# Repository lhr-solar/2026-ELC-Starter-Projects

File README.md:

# 2026-ELC-Starter-Projects

## Goals
- Familiarize yourself with the basics of KiCad
- Learn how to make a schematic and place components into a layout
- Get used to submitting reviews, working on projects outside of workday, and using GitHub

## Repo Instructions
1. Clone the repo to your local machine
   
   ```git clone git@github.com:lhr-solar/2026-ELC-Starter-Projects.git```
2. In the repo, create a new branch with your name and check that the branch exists on the remote repo as well

   ```git checkout -b bevo```
3. Create a new KiCad project inside the folder with your name. When you create the project, make sure you DO NOT check the box that creates a new folder for the project.
4. Push your changes to the remote repository. Here are the commands you'll need to use + a more detailed [github guide](https://app.notion.com/p/lhrs/How-to-Git-3506309905da81729984d78645f975d0?source=copy_link)
   
   ``` git status``` -> Shows you the status report for all the files in your directory. Confirm that you're on the correct branch and NOT MAIN
   
   ``` git add .``` -> Adds all new, modified, and deleted files to the staging area (local action)
   
   ``` git commit -m "wow I made a repo"``` -> Saves a snapshot of the files from the staging area with a message (local action)
   
   ``` git push``` -> Saves the snapshot to the remote repo so everyone else can see your changes (remote action)
   
6. Follow the tutorials and keep learning! Push your changes frequently so you don't accidentally lose your progress if KiCad crashes (trust us on this one... it's not fun)

## Schematic
https://www.youtube.com/watch?v=nkHFoxe0mrU

Don't worry if his KiCad looks different from yours, this was made in 7 and we're using 10.

## Layout
https://www.youtube.com/watch?v=PlXd3lLZ4vc

Try to attempt the layout yourself before trying Phil's version. Make sure you push your trial run to Github before redoing it with Phil

## Advice
- Ask tons of questions! Make them public so everyone can learn!
- Come to review council to talk through your designs and reasoning
- Question everything! Learn why we do things a certain way so that you become a better engineer

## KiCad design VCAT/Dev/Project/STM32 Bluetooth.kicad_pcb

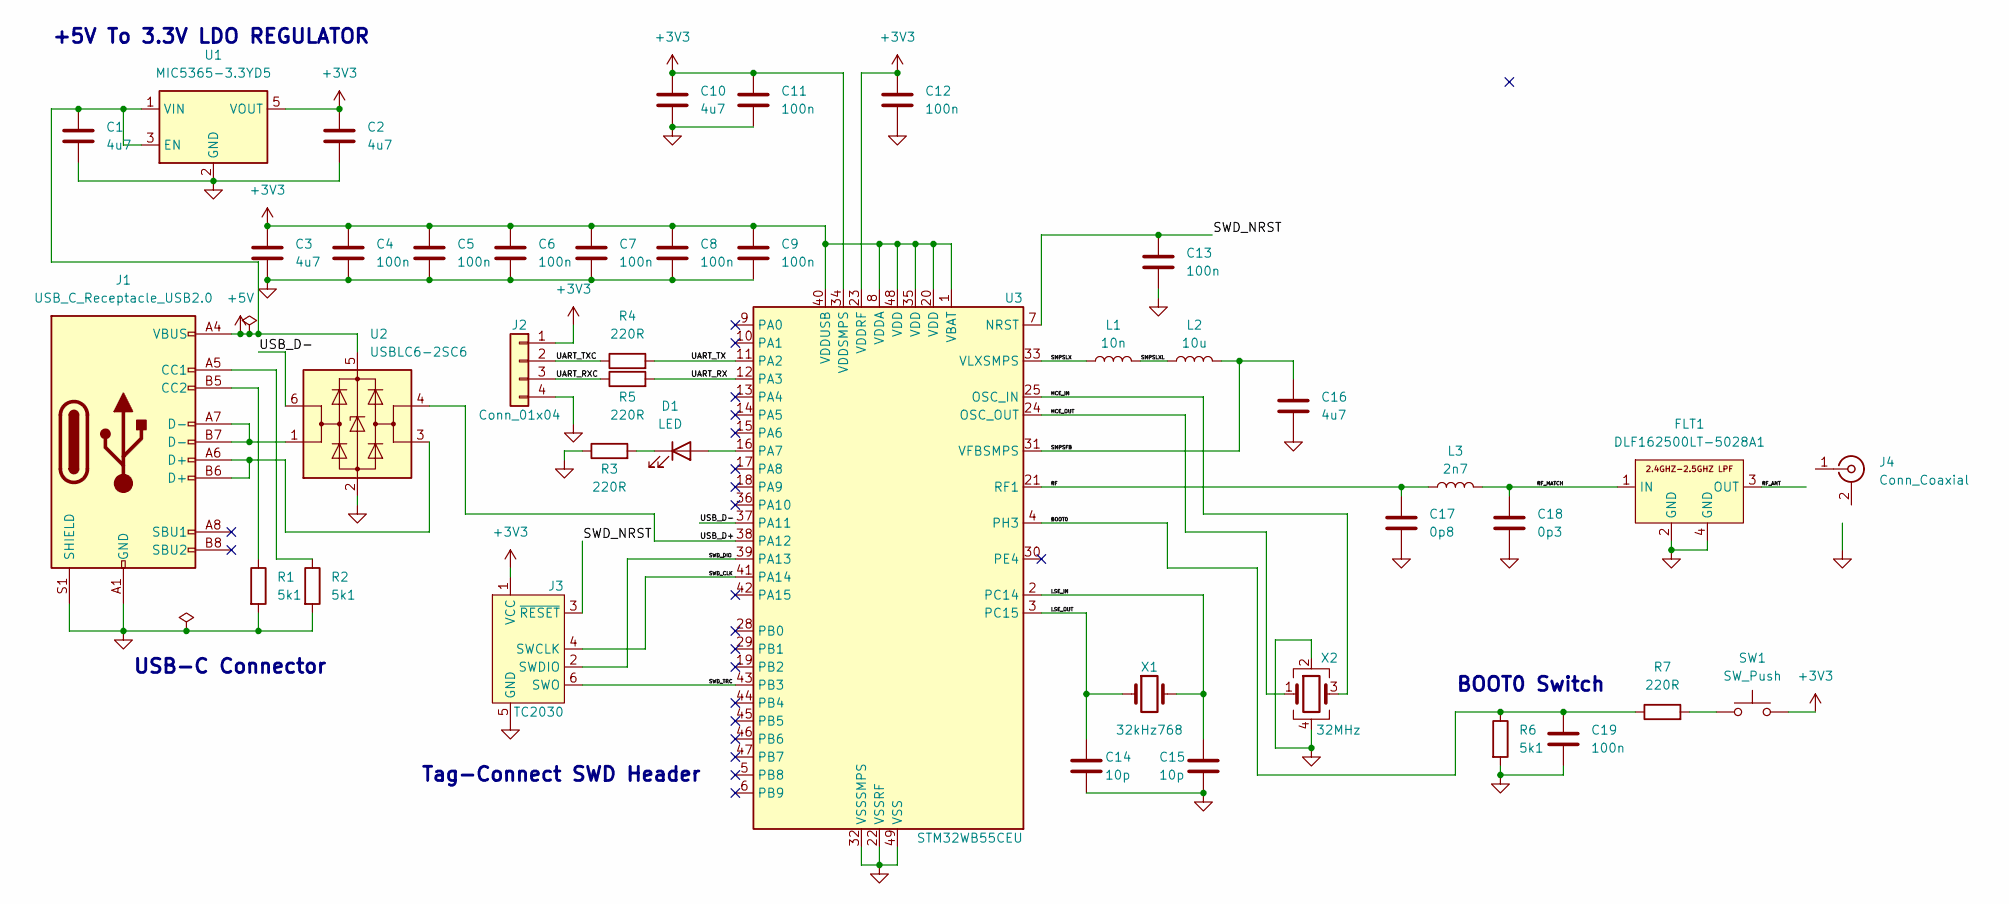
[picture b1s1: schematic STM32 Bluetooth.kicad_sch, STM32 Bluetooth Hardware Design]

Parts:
C1, C2, C3, C10, C16: 4u7; C_0603_1608Metric
C4, C5, C6, C7, C8, C9, C11, C12, C13, C19: 100n; C_0402_1005Metric
C14, C15: 10p; C_0402_1005Metric
C17: 0p8; C_0402_1005Metric
C18: 0p3; C_0402_1005Metric
D1: LED; LED_0402_1005Metric
FLT1: DLF162500LT-5028A1
J1: USB_C_Receptacle_USB2.0; USB_C_Receptacle_GCT_USB4105-xx-A_16P_TopMnt_Horizontal
J2: Conn_01x04; Molex_PicoBlade_53048-0410_1x04_P1.25mm_Horizontal
J3: TC2030; Tag-Connect_TC2030-IDC-FP_2x03_P1.27mm_Vertical
J4: Conn_Coaxial; U.FL_Hirose_U.FL-R-SMT-1_Vertical
L1: 10n; L_0402_1005Metric
L2: 10u; L_0805_2012Metric
L3: 2n7; L_0402_1005Metric
R1, R2, R6: 5k1; R_0402_1005Metric
R3, R4, R5, R7: 220R; R_0402_1005Metric
SW1: SW_Push; SW_SPST_CK_RS282G05A3
U1: MIC5365-3.3YD5; SOT-23-5
U2: USBLC6-2SC6; SOT-23-6
U3: STM32WB55CEU; QFN-48-1EP_7x7mm_P0.5mm_EP5.6x5.6mm
X1: 32kHz768; Crystal_SMD_2012-2Pin_2.0x1.2mm
X2: 32MHz; Crystal_SMD_2016-4Pin_2.0x1.6mm

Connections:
+3V3: C2.1, C3.1, C4.1, C5.1, C6.1, C7.1, C8.1, C9.1, C10.1, C11.1, C12.1, J2.1, J3.1 (VCC), SW1.2, U1.5 (VOUT), U3.1 (VBAT), U3.8 (VDDA), U3.20 (VDD), U3.23 (VDDRF), U3.34 (VDDSMPS), U3.35 (VDD), U3.40 (VDDUSB), U3.48 (VDD)
+5V: C1.1, J1.A4 (VBUS), J1.A9 (VBUS), J1.B4 (VBUS), J1.B9 (VBUS), U1.1 (VIN), U1.3 (EN), U2.5 (VBUS)
/BOOT0: C19.1, R6.1, R7.1, U3.4 (PH3)
/HCE_IN: U3.25 (OSC_IN), X2.3
/HCE_OUT: U3.24 (OSC_OUT), X2.1
/LSE_IN: C15.1, U3.2 (PC14), X1.2
/LSE_OUT: C14.1, U3.3 (PC15), X1.1
/RF: C17.1, L3.1, U3.21 (RF1)
/RF_ANT: FLT1.3 (OUT), J4.1 (In)
/RF_MATCH: C18.1, FLT1.1 (IN), L3.2
/SMPSFB: C16.1, L2.2, U3.31 (VFBSMPS)
/SMPSLX: L1.1, U3.33 (VLXSMPS)
/SMPSLXL: L1.2, L2.1
/SWD_CLK: J3.4 (SWCLK), U3.41 (PA14)
/SWD_DIO: J3.2 (SWDIO), U3.39 (PA13)
/SWD_NRST: C13.1, J3.3 (~RESET), U3.7 (NRST)
/SWD_TRC: J3.6 (SWO), U3.43 (PB3)
/UART_RX: R5.2, U3.12 (PA3)
/UART_RXC: J2.3, R5.1
/UART_TX: R4.2, U3.11 (PA2)
/UART_TXC: J2.2, R4.1
/USB_D+: U2.4 (I/O2), U3.38 (PA12)
/USB_D-: U2.6 (I/O1), U3.37 (PA11)
GND: C1.2, C2.2, C3.2, C4.2, C5.2, C6.2, C7.2, C8.2, C9.2, C10.2, C11.2, C12.2, C13.2, C14.2, C15.2, C16.2, C17.2, C18.2, C19.2, FLT1.2 (GND), FLT1.4 (GND), J1.A1 (GND), J1.A12 (GND), J1.B1 (GND), J1.B12 (GND), J1.S1 (SHIELD), J2.4, J3.5 (GND), J4.2 (Ext), R1.2, R2.2, R3.1, R6.2, U1.2 (GND), U2.2 (GND), U3.22 (VSSRF), U3.32 (VSSSMPS), U3.49 (VSS), X2.2, X2.4
unnamed: D1.2 (A), U3.16 (PA7)
unnamed: D1.1 (K), R3.2
unnamed: J1.A5 (CC1), R2.1
unnamed: J1.B5 (CC2), R1.1
unnamed: J1.A6 (D+), J1.B6 (D+), U2.3 (I/O2)
unnamed: J1.A7 (D-), J1.B7 (D-), U2.1 (I/O1)
unnamed: R7.2, SW1.1

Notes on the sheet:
Tag-Connect SWD Header
BOOT0 Switch
+5V To 3.3V LDO REGULATOR
USB-C Connector

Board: 4 copper layers, 41 parts (0 on the bottom side), 31 nets, no tracks yet.

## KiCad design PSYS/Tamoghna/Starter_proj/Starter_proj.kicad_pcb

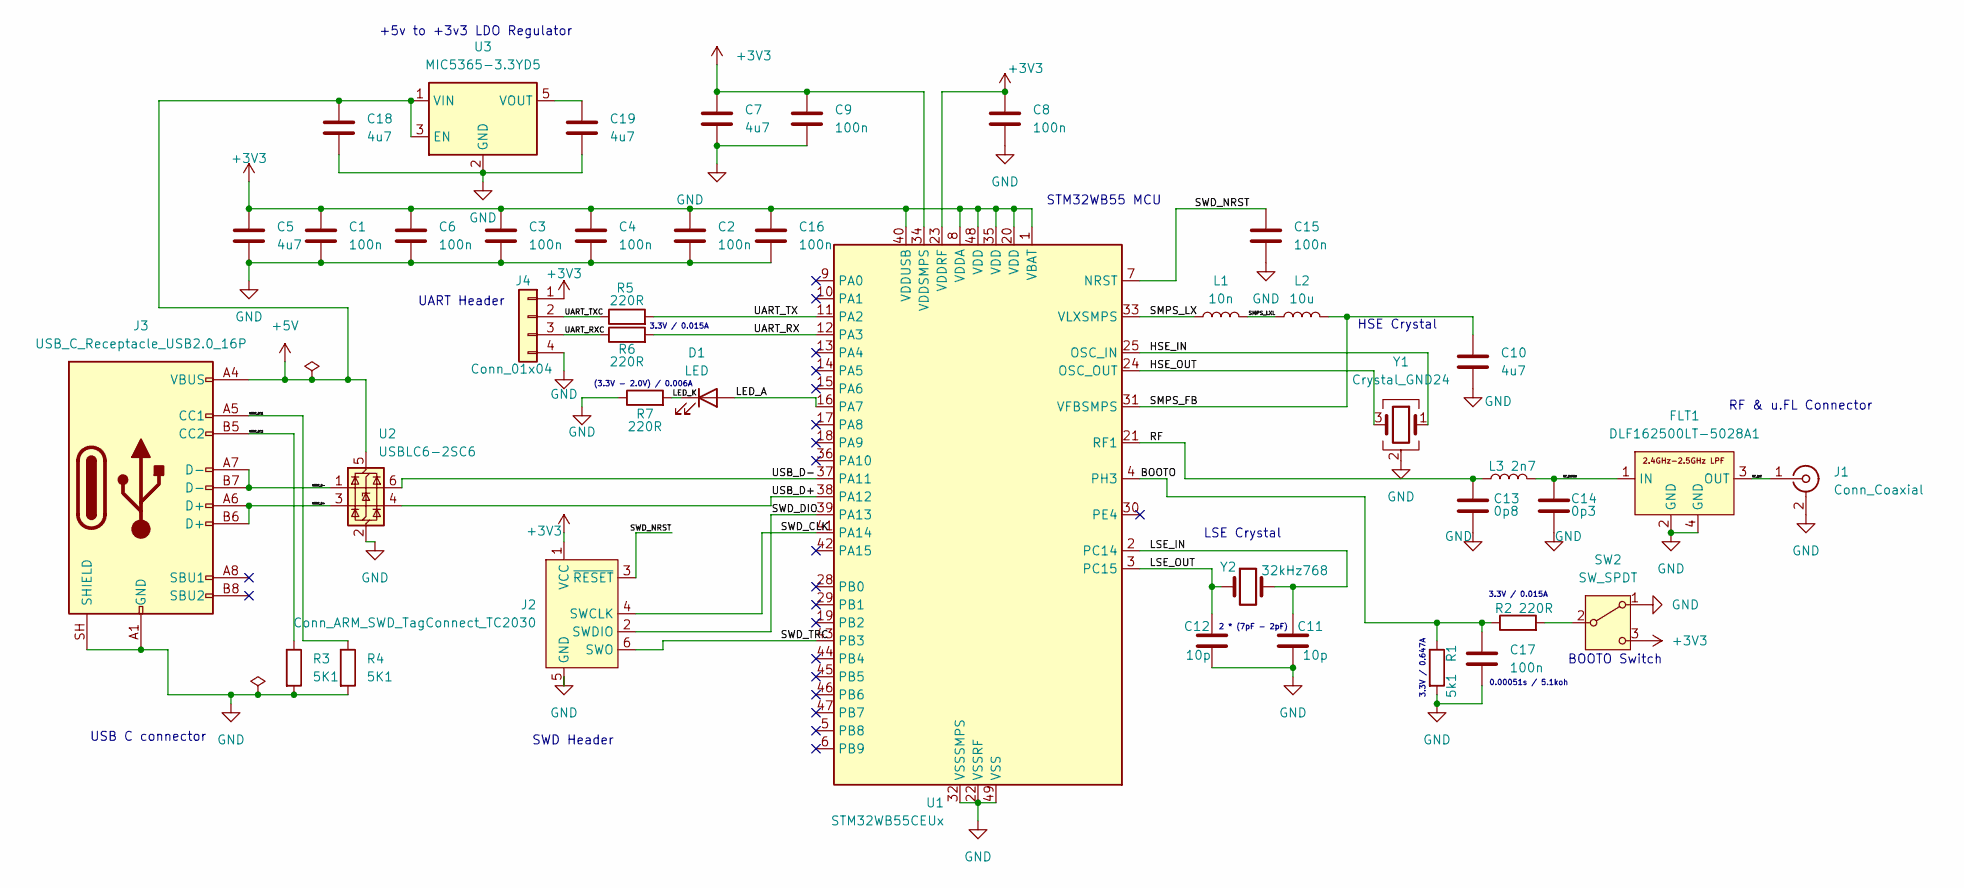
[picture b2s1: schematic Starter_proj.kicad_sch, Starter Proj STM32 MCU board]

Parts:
C1, C2, C3, C4, C6, C8, C9, C15, C16, C17: 100n; C_0603_1608Metric
C5, C7, C10, C18, C19: 4u7; C_0805_2012Metric
C11, C12: 10p; C_0402_1005Metric
C13: 0p8; C_0402_1005Metric
C14: 0p3; C_0402_1005Metric
D1: LED; LED_0603_1608Metric
FLT1: DLF162500LT-5028A1; Untitled
J1: Conn_Coaxial; U.FL_Hirose_U.FL-R-SMT-1_Vertical
J2: Conn_ARM_SWD_TagConnect_TC2030; Tag-Connect_TC2030-IDC-FP_2x03_P1.27mm_Vertical
J3: USB_C_Receptacle_USB2.0_16P; USB_C_Receptacle_GCT_USB4105-xx-A_16P_TopMnt_Horizontal
J4: Conn_01x04; Molex_PicoBlade_53047-0410_1x04_P1.25mm_Vertical
L1: 10n; L_0402_1005Metric
L2: 10u; L_0805_2012Metric
L3: 2n7; L_0402_1005Metric
R1: 5k1; R_0603_1608Metric
R2, R5, R6, R7: 220R; R_0603_1608Metric
R3, R4: 5K1; R_0603_1608Metric
SW2: SW_SPDT; SW_Wurth_WS-SLSV_450406020024
U1: STM32WB55CEUx; QFN-48-1EP_7x7mm_P0.5mm_EP5.6x5.6mm
U2: USBLC6-2SC6; SOT-23-6
U3: MIC5365-3.3YD5; TSOT-23-5
Y1: Crystal_GND24; Crystal_SMD_2016-4Pin_2.0x1.6mm
Y2: 32kHz768; Crystal_SMD_3215-2Pin_3.2x1.5mm

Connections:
+3V3: C1.1, C2.1, C3.1, C4.1, C5.1, C6.1, C7.1, C8.1, C9.1, C16.1, J2.1 (VCC), J4.1, SW2.3 (C), U1.1 (VBAT), U1.8 (VDDA), U1.20 (VDD), U1.23 (VDDRF), U1.34 (VDDSMPS), U1.35 (VDD), U1.40 (VDDUSB), U1.48 (VDD)
+5V: C18.1, J3.A4 (VBUS), J3.A9 (VBUS), J3.B4 (VBUS), J3.B9 (VBUS), U2.5 (VBUS), U3.1 (VIN), U3.3 (EN)
/BOOTO: C17.1, R1.1, R2.1, U1.4 (PH3)
/HSE_IN: U1.25 (OSC_IN), Y1.1
/HSE_OUT: U1.24 (OSC_OUT), Y1.3
/LED_A: D1.2 (A), U1.16 (PA7)
/LED_K: D1.1 (K), R7.2
/LSE_IN: C11.1, U1.2 (PC14), Y2.2
/LSE_OUT: C12.1, U1.3 (PC15), Y2.1
/RF: C13.1, L3.1, U1.21 (RF1)
/RF_ANT: FLT1.3 (OUT), J1.1 (In)
/RF_MATCH: C14.1, FLT1.1 (IN), L3.2
/SMPS_FB: C10.1, L2.2, U1.31 (VFBSMPS)
/SMPS_LX: L1.1, U1.33 (VLXSMPS)
/SMPS_LXL: L1.2, L2.1
/SWD_CLK: J2.4 (SWCLK), U1.41 (PA14)
/SWD_DIO: J2.2 (SWDIO), U1.39 (PA13)
/SWD_NRST: C15.1, J2.3 (~RESET), U1.7 (NRST)
/SWD_TRC: J2.6 (SWO), U1.43 (PB3)
/UART_RX: R6.2, U1.12 (PA3)
/UART_RXC: J4.3, R6.1
/UART_TX: R5.2, U1.11 (PA2)
/UART_TXC: J4.2, R5.1
/USBC_CC1: J3.A5 (CC1), R4.1
/USBC_CC2: J3.B5 (CC2), R3.1
/USBC_D+: J3.A6 (D+), J3.B6 (D+), U2.3 (I/O2)
/USBC_D-: J3.A7 (D-), J3.B7 (D-), U2.1 (I/O1)
/USB_D+: U1.38 (PA12), U2.4 (I/O2)
/USB_D-: U1.37 (PA11), U2.6 (I/O1)
GND: C1.2, C2.2, C3.2, C4.2, C5.2, C6.2, C7.2, C8.2, C9.2, C10.2, C11.2, C12.2, C13.2, C14.2, C15.2, C16.2, C17.2, C18.2, C19.2, FLT1.2 (GND), FLT1.4 (GND), J1.2 (Ext), J2.5 (GND), J3.A1 (GND), J3.A12 (GND), J3.B1 (GND), J3.B12 (GND), J3.SH (SHIELD), J4.4, R1.2, R3.2, R4.2, R7.1, SW2.1 (A), U1.22 (VSSRF), U1.32 (VSSSMPS), U1.49 (VSS), U2.2 (GND), U3.2 (GND), Y1.2 (G), Y1.4 (G)
unnamed: R2.2, SW2.2 (B)
unnamed: C19.1, U3.5 (VOUT)

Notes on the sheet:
3.3V / 0.647A
+5v to +3v3 LDO Regulator
BOOTO Switch
USB C connector
3.3V / 0.015A
0.00051s / 5.1koh
SWD Header
STM32WB55 MCU
UART Header
3.3V / 0.015A
2 * (7pF - 2pF)
RF & u.FL Connector
HSE Crystal
LSE Crystal
(3.3V - 2.0V) / 0.006A

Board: 4 copper layers, 41 parts (0 on the bottom side), 32 nets, no tracks yet.
